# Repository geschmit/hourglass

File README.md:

# Hourglass
Hourglass is a custom PCB watch designed in KiCAD 7.0, to be funded by the Hack Club [OnBoard](https://github.com/hackclub/OnBoard/) grant, which allocates $100 for high schoolers to design and build their own custom PCBs.

## Features
- Accelerometer & Magnetometer for detecting orientation and movement
- 60 individual LEDs for displaying minutes & seconds
- RTC for high-precision timekeeping
- Programmable user buttons
- Revision A:
  - FIDO2 Authentication token
  - USB-C interface
- Revision B:
  - Cheap manufacturing cost

## Revisions
### [Revision A:](./hourglass_reva/) Working design iteration
> `Status: ✔️ (COMPLETE)`

Revision A is the original design, based on the Atmel ATMega32u4 microcontroller. It features a RTC and 9DoF magnetometer-accelerometer to detect orientation, magnetic field strength and more to act as both a device for keeping time and sense when the wearer has raised the watchface to observe. In addition, a USB-C port can allow for interfacing directly to the Mega for uploading code and other functions.

### [Revision B:](./hourglass_revb/) Cost-effective design
> `Status: ✔️ (COMPLETE)`

Revision B is a easier, more affordable option. I'm working on this primarily because revision A is simply too expensive with all peripherals added in to have assembled via JLC's PCBA. It swaps the ATMega32 with an RP2040, the 9DoF magnetometer with split magnetometer & accelerometer ICs, and forgoes the rear battery slot alltogether. The caveat with this is you'll need to wire a battery to the device yourself, but comes at a tremendous discount with the requirement for dual-sided PCB assembly forgone.

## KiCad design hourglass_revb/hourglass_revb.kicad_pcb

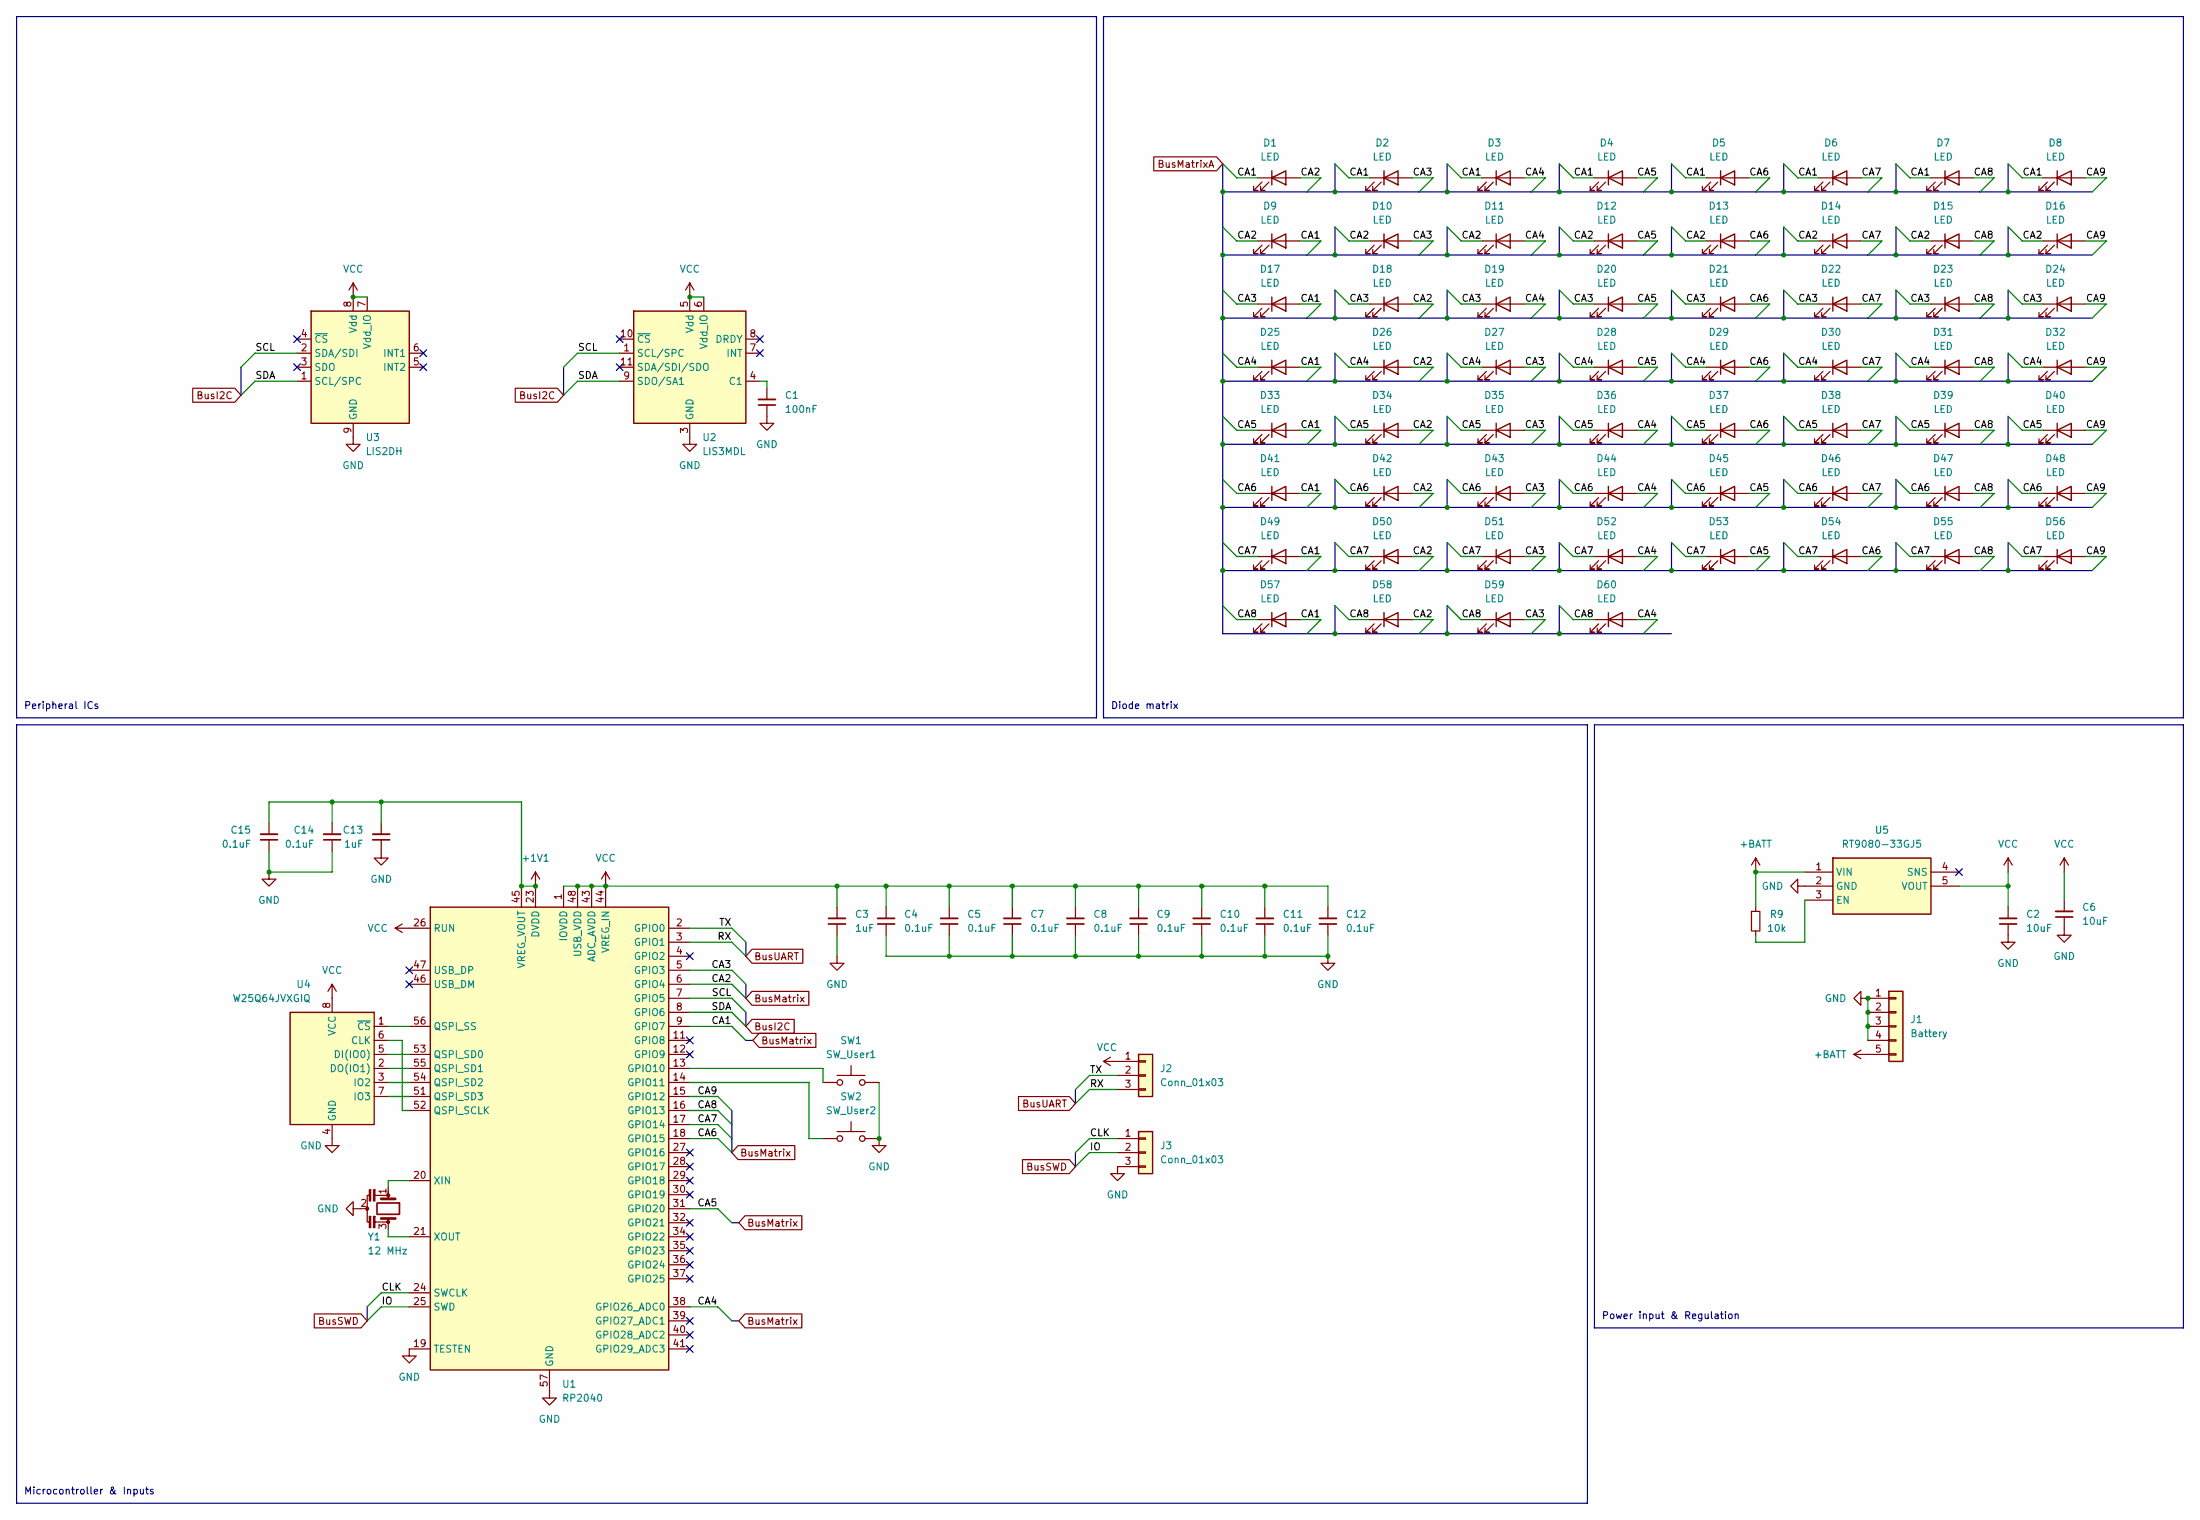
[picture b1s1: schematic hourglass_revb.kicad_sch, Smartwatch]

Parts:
C1: 100nF; C_0201_0603Metric
C2, C6: 10uF; C_0201_0603Metric
C3, C13: 1uF; C_0201_0603Metric
C4, C5, C7, C8, C9, C10, C11, C12, C14, C15: 0.1uF; C_0201_0603Metric
D1, D6, D11, D16, D21, D26, D31, D36, D41, D46, D51, D56: LED; LED_0603_1608Metric
D2, D3, D4, D5, D7, D8, D9, D10, D12, D13, D14, D15, D17, D18, D19, D20, D22, D23, D24, D25, D27, D28, D29, D30, D32, D33, D34, D35, D37, D38, D39, D40, D42, D43, D44, D45, D47, D48, D49, D50, D52, D53, D54, D55, D57, D58, D59, D60: LED; LED_0402_1005Metric
J1: Battery; BAT_BAT-HLD-001-THM
J2, J3: Conn_01x03; PinHeader_1x03_P2.54mm_Vertical
R9: 10k; R_0201_0603Metric
SW1: SW_User1; SW_Push_SPST_NO_Alps_SKRK
SW2: SW_User2; SW_Push_SPST_NO_Alps_SKRK
U1: RP2040; QFN-56-1EP_7x7mm_P0.4mm_EP3.2x3.2mm
U2: LIS3MDL; LGA-12_2x2mm_P0.5mm
U3: LIS2DH; LGA-14_2x2mm_P0.35mm_LayoutBorder3x4y
U4: W25Q64JVXGIQ; WSON-8-1EP_6x5mm_P1.27mm_EP3.4x4.3mm
U5: RT9080-33GJ5; SOT94P280X100-5N; Manufacturer_Part_Number RT9080-33GJ5; Mouser Part Number 835-RT9080-33GJ5
Y1: 12 MHz; ABM8272T3

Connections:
+1V1: C13.2, C14.2, C15.2, U1.23 (DVDD), U1.45 (VREG_VOUT), U1.50 (DVDD)
+BATT: J1.5, R9.1, U5.1 (VIN)
/CA1: D1.1 (K), D2.1 (K), D3.1 (K), D4.1 (K), D5.1 (K), D6.1 (K), D7.1 (K), D8.1 (K), D9.2 (A), D17.2 (A), D25.2 (A), D33.2 (A), D41.2 (A), D49.2 (A), D57.2 (A), U1.9 (GPIO7)
/CA2: D1.2 (A), D9.1 (K), D10.1 (K), D11.1 (K), D12.1 (K), D13.1 (K), D14.1 (K), D15.1 (K), D16.1 (K), D18.2 (A), D26.2 (A), D34.2 (A), D42.2 (A), D50.2 (A), D58.2 (A), U1.6 (GPIO4)
/CA3: D2.2 (A), D10.2 (A), D17.1 (K), D18.1 (K), D19.1 (K), D20.1 (K), D21.1 (K), D22.1 (K), D23.1 (K), D24.1 (K), D27.2 (A), D35.2 (A), D43.2 (A), D51.2 (A), D59.2 (A), U1.5 (GPIO3)
/CA4: D3.2 (A), D11.2 (A), D19.2 (A), D25.1 (K), D26.1 (K), D27.1 (K), D28.1 (K), D29.1 (K), D30.1 (K), D31.1 (K), D32.1 (K), D36.2 (A), D44.2 (A), D52.2 (A), D60.2 (A), U1.38 (GPIO26_ADC0)
/CA5: D4.2 (A), D12.2 (A), D20.2 (A), D28.2 (A), D33.1 (K), D34.1 (K), D35.1 (K), D36.1 (K), D37.1 (K), D38.1 (K), D39.1 (K), D40.1 (K), D45.2 (A), D53.2 (A), U1.31 (GPIO20)
/CA6: D5.2 (A), D13.2 (A), D21.2 (A), D29.2 (A), D37.2 (A), D41.1 (K), D42.1 (K), D43.1 (K), D44.1 (K), D45.1 (K), D46.1 (K), D47.1 (K), D48.1 (K), D54.2 (A), U1.18 (GPIO15)
/CA7: D6.2 (A), D14.2 (A), D22.2 (A), D30.2 (A), D38.2 (A), D46.2 (A), D49.1 (K), D50.1 (K), D51.1 (K), D52.1 (K), D53.1 (K), D54.1 (K), D55.1 (K), D56.1 (K), U1.17 (GPIO14)
/CA8: D7.2 (A), D15.2 (A), D23.2 (A), D31.2 (A), D39.2 (A), D47.2 (A), D55.2 (A), D57.1 (K), D58.1 (K), D59.1 (K), D60.1 (K), U1.16 (GPIO13)
/CA9: D8.2 (A), D16.2 (A), D24.2 (A), D32.2 (A), D40.2 (A), D48.2 (A), D56.2 (A), U1.15 (GPIO12)
/CLK: J3.1, U1.24 (SWCLK)
/IO: J3.2, U1.25 (SWD)
/RX: J2.3, U1.3 (GPIO1)
/SCL: U1.7 (GPIO5), U2.1 (SCL/SPC), U3.2 (SDA/SDI)
/SDA: U1.8 (GPIO6), U2.9 (SDO/SA1), U3.1 (SCL/SPC)
/TX: J2.2, U1.2 (GPIO0)
GND: C1.1, C2.1, C3.1, C4.1, C5.1, C6.1, C7.1, C8.1, C9.1, C10.1, C11.1, C12.1, C13.1, C14.1, C15.1, J1.1, J1.2, J1.3, J1.4, J3.3, SW1.2, SW2.2, U1.19 (TESTEN), U1.57 (GND), U2.2 (GND), U2.3 (GND), U2.12 (GND), U3.9 (GND), U3.10 (GND), U3.11 (GND), U3.12 (GND), U3.13 (GND), U3.14 (GND), U4.4 (GND), U5.2 (GND), Y1.2
unnamed: SW1.1, U1.13 (GPIO10)
unnamed: SW2.1, U1.14 (GPIO11)
unnamed: U1.52 (QSPI_SCLK), U4.6 (CLK)
unnamed: U1.53 (QSPI_SD0), U4.5 (DI(IO0))
unnamed: U1.55 (QSPI_SD1), U4.2 (DO(IO1))
unnamed: U1.54 (QSPI_SD2), U4.3 (IO2)
unnamed: U1.51 (QSPI_SD3), U4.7 (IO3)
unnamed: U1.56 (QSPI_SS), U4.1 (~CS)
unnamed: U1.20 (XIN), Y1.1
unnamed: U1.21 (XOUT), Y1.3
unnamed: C1.2, U2.4 (C1)
unnamed: R9.2, U5.3 (EN)
VCC: C2.2, C3.2, C4.2, C5.2, C6.2, C7.2, C8.2, C9.2, C10.2, C11.2, C12.2, J2.1, U1.1 (IOVDD), U1.10 (IOVDD), U1.22 (IOVDD), U1.26 (RUN), U1.33 (IOVDD), U1.42 (IOVDD), U1.43 (ADC_AVDD), U1.44 (VREG_IN), U1.48 (USB_VDD), U1.49 (IOVDD), U2.5 (Vdd), U2.6 (Vdd_IO), U3.7 (Vdd_IO), U3.8 (Vdd), U4.8 (VCC), U5.5 (VOUT)

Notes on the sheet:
Power input & Regulation
Diode matrix
Peripheral ICs
Microcontroller & Inputs

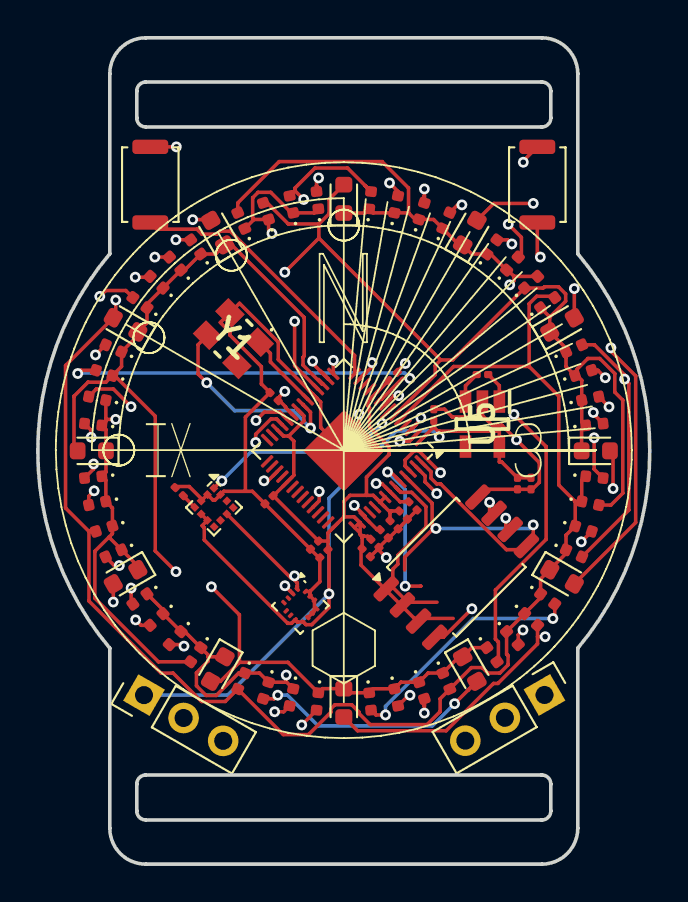
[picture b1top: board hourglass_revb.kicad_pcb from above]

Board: 4 copper layers, 34.0 x 45.9 mm, 87 parts (1 on the bottom side), 31 nets.

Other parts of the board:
kibuzzard-66C6528B: G***; kibuzzard-66C6528B

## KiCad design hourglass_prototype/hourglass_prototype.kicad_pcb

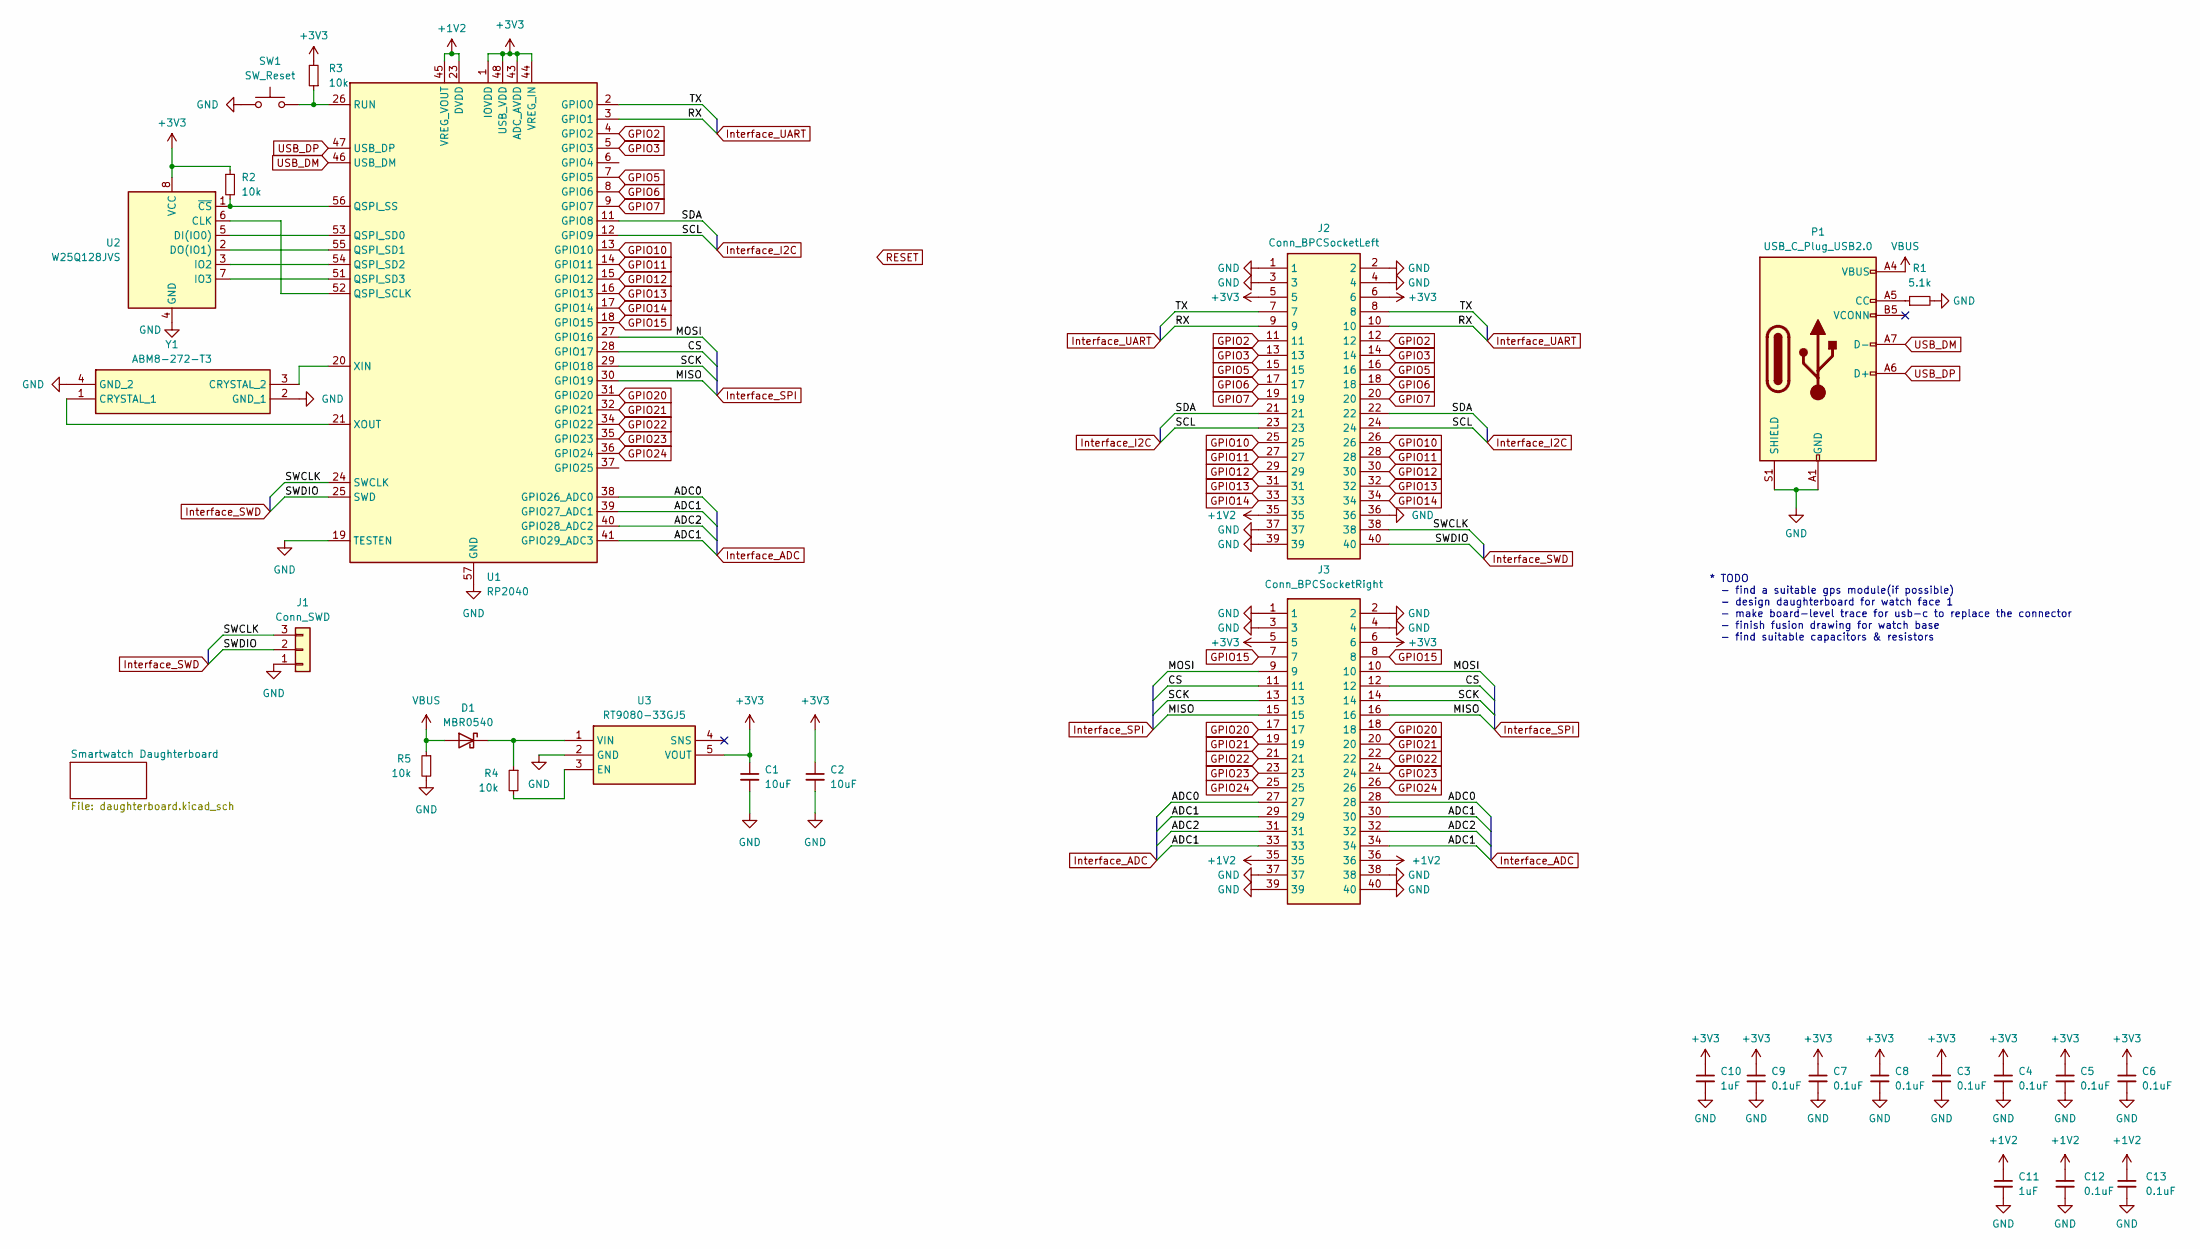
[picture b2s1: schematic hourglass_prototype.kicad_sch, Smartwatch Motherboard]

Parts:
C1, C2: 10uF; C_0201_0603Metric
C3, C4, C5, C6, C7, C8, C9, C12, C13: 0.1uF; C_0201_0603Metric
C10, C11: 1uF; C_0201_0603Metric
D1: MBR0540; D_SOD-123
J1: Conn_SWD; JST_SH_BM03B-SRSS-TB_1x03-1MP_P1.00mm_Vertical
J2: Conn_BPCSocketLeft; DF40HC3040DS04V51; Manufacturer_Part_Number DF40HC(3.0)-40DS-0.4V(51); Mouser Part Number 798-DF40HC3040DS04V5
J3: Conn_BPCSocketRight; DF40HC3040DS04V51; Manufacturer_Part_Number DF40HC(3.0)-40DS-0.4V(51); Mouser Part Number 798-DF40HC3040DS04V5
P1: USB_C_Plug_USB2.0; USB_C_Receptacle_GCT_USB4105-xx-A_16P_TopMnt_Horizontal
R1: 5.1k; R_0201_0603Metric
R2, R3, R4, R5: 10k; R_0201_0603Metric
SW1: SW_Reset
U1: RP2040; QFN-56-1EP_7x7mm_P0.4mm_EP3.2x3.2mm
U2: W25Q128JVS; SOIC127P790X216-8N
U3: RT9080-33GJ5; SOT94P280X100-5N; Manufacturer_Part_Number RT9080-33GJ5; Mouser Part Number 835-RT9080-33GJ5
Y1: ABM8-272-T3; ABM8272T3; Manufacturer_Part_Number ABM8-272-T3; Mouser Part Number 815-ABM8-272-T3

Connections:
+3V3: C1.1, C2.1, C3.1, C4.1, C5.1, C6.1, C7.1, C8.1, C9.1, C10.1, J2.5, J2.6, J3.5, J3.6, R2.1, R3.2, U1.1 (IOVDD), U1.10 (IOVDD), U1.22 (IOVDD), U1.33 (IOVDD), U1.42 (IOVDD), U1.43 (ADC_AVDD), U1.44 (VREG_IN), U1.48 (USB_VDD), U1.49 (IOVDD), U2.8 (VCC), U3.5 (VOUT); also elsewhere on the board
/ADC0: J3.27, J3.28, U1.38 (GPIO26_ADC0)
/ADC2: J3.31, J3.32, U1.40 (GPIO28_ADC2)
/CS: J3.11, J3.12, U1.28 (GPIO17)
/MISO: J3.15, J3.16, U1.30 (GPIO19)
/MOSI: J3.9, J3.10, U1.27 (GPIO16)
/RX: J2.9, J2.10, U1.3 (GPIO1)
/SCK: J3.13, J3.14, U1.29 (GPIO18)
/SCL: J2.23, J2.24, U1.12 (GPIO9)
/SDA: J2.21, J2.22, U1.11 (GPIO8)
/SWCLK: J1.3, J2.38, U1.24 (SWCLK)
/SWDIO: J1.2, J2.40, U1.25 (SWD)
/TX: J2.7, J2.8, U1.2 (GPIO0)
GPIO2: J2.11, J2.12, U1.4 (GPIO2); also elsewhere on the board
GPIO3: J2.13, J2.14, U1.5 (GPIO3); also elsewhere on the board
GPIO5: J2.15, J2.16, U1.7 (GPIO5); also elsewhere on the board
GPIO6: J2.17, J2.18, U1.8 (GPIO6); also elsewhere on the board
GPIO7: J2.19, J2.20, U1.9 (GPIO7); also elsewhere on the board
GPIO10: J2.25, J2.26, U1.13 (GPIO10); also elsewhere on the board
GPIO11: J2.27, J2.28, U1.14 (GPIO11); also elsewhere on the board
GPIO12: J2.29, J2.30, U1.15 (GPIO12); also elsewhere on the board
GPIO13: J2.31, J2.32, U1.16 (GPIO13); also elsewhere on the board
GPIO14: J2.33, J2.34, U1.17 (GPIO14); also elsewhere on the board
GPIO15: J3.7, J3.8, U1.18 (GPIO15); also elsewhere on the board
GPIO20: J3.17, J3.18, U1.31 (GPIO20); also elsewhere on the board
GPIO21: J3.19, J3.20, U1.32 (GPIO21); also elsewhere on the board
GPIO22: J3.21, J3.22, U1.34 (GPIO22); also elsewhere on the board
GPIO23: J3.23, J3.24, U1.35 (GPIO23); also elsewhere on the board
GPIO24: J3.25, J3.26, U1.36 (GPIO24); also elsewhere on the board
unnamed: D1.1 (K), R4.1, U3.1 (VIN)
unnamed: P1.A5 (CC), R1.1
unnamed: U1.52 (QSPI_SCLK), U2.6 (CLK)
unnamed: U1.53 (QSPI_SD0), U2.5 (DI(IO0))
unnamed: U1.55 (QSPI_SD1), U2.2 (DO(IO1))
unnamed: U1.54 (QSPI_SD2), U2.3 (IO2)
unnamed: U1.51 (QSPI_SD3), U2.7 (IO3)
unnamed: R2.2, U1.56 (QSPI_SS), U2.1 (~CS)
unnamed: R3.1, SW1.2, U1.26 (RUN)
unnamed: U1.20 (XIN), Y1.3 (CRYSTAL_2)
unnamed: U1.21 (XOUT), Y1.1 (CRYSTAL_1)
unnamed: R4.2, U3.3 (EN)
USB_DM: P1.A7 (D-), U1.46 (USB_DM)
USB_DP: P1.A6 (D+), U1.47 (USB_DP)
VBUS: D1.2 (A), P1.A4 (VBUS), P1.A9 (VBUS), P1.B4 (VBUS), P1.B9 (VBUS), R5.1

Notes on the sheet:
* TODO - find a suitable gps module(if possible) - design daughterboard for watch face 1 - make board-level trace for usb-c to replace the connector - finish fusion drawing for watch base - find suitable capacitors & resistors

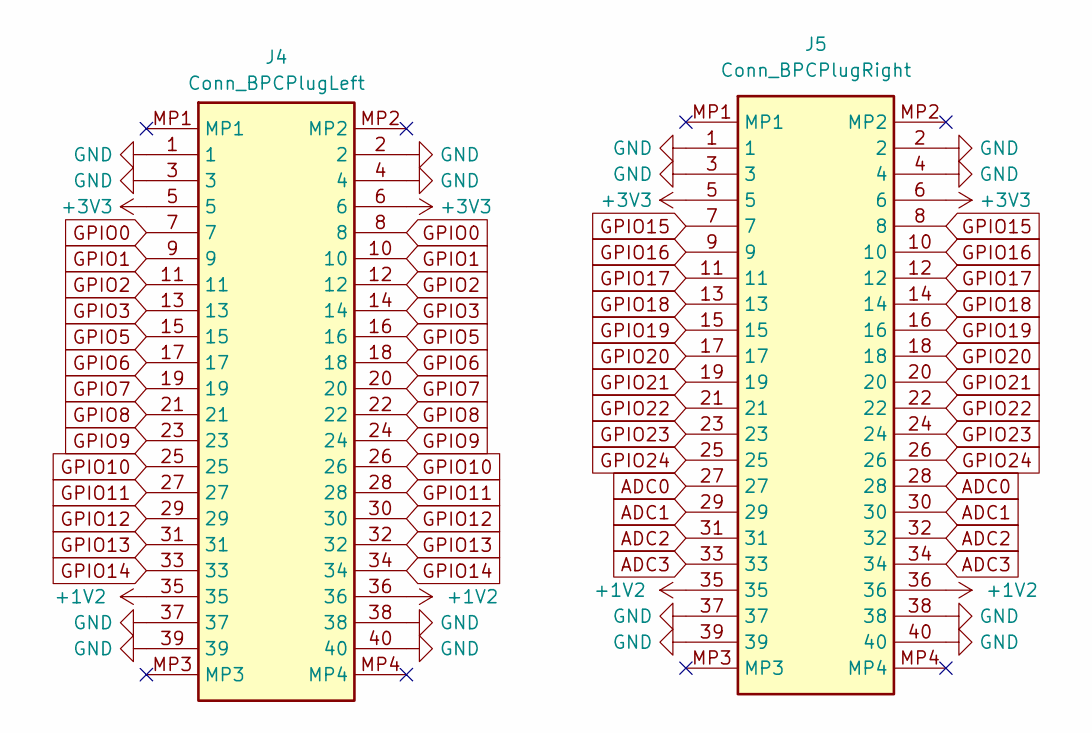
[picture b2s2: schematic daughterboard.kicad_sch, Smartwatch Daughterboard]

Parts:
J4: Conn_BPCPlugLeft; DF40C40DP04V51; Manufacturer_Part_Number DF40C-40DP-0.4V(51); Mouser Part Number 798-DF40C40DP0.4V51
J5: Conn_BPCPlugRight; DF40C40DP04V51; Manufacturer_Part_Number DF40C-40DP-0.4V(51); Mouser Part Number 798-DF40C40DP0.4V51

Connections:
+3V3: J4.5, J4.6, J5.5, J5.6; also elsewhere on the board
ADC0: J5.27, J5.28
ADC1: J5.29, J5.30
ADC2: J5.31, J5.32
ADC3: J5.33, J5.34
GPIO0: J4.7, J4.8
GPIO1: J4.9, J4.10
GPIO2: J4.11, J4.12; also elsewhere on the board
GPIO3: J4.13, J4.14; also elsewhere on the board
GPIO5: J4.15, J4.16; also elsewhere on the board
GPIO6: J4.17, J4.18; also elsewhere on the board
GPIO7: J4.19, J4.20; also elsewhere on the board
GPIO8: J4.21, J4.22
GPIO9: J4.23, J4.24
GPIO10: J4.25, J4.26; also elsewhere on the board
GPIO11: J4.27, J4.28; also elsewhere on the board
GPIO12: J4.29, J4.30; also elsewhere on the board
GPIO13: J4.31, J4.32; also elsewhere on the board
GPIO14: J4.33, J4.34; also elsewhere on the board
GPIO15: J5.7, J5.8; also elsewhere on the board
GPIO16: J5.9, J5.10
GPIO17: J5.11, J5.12
GPIO18: J5.13, J5.14
GPIO19: J5.15, J5.16
GPIO20: J5.17, J5.18; also elsewhere on the board
GPIO21: J5.19, J5.20; also elsewhere on the board
GPIO22: J5.21, J5.22; also elsewhere on the board
GPIO23: J5.23, J5.24; also elsewhere on the board
GPIO24: J5.25, J5.26; also elsewhere on the board

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
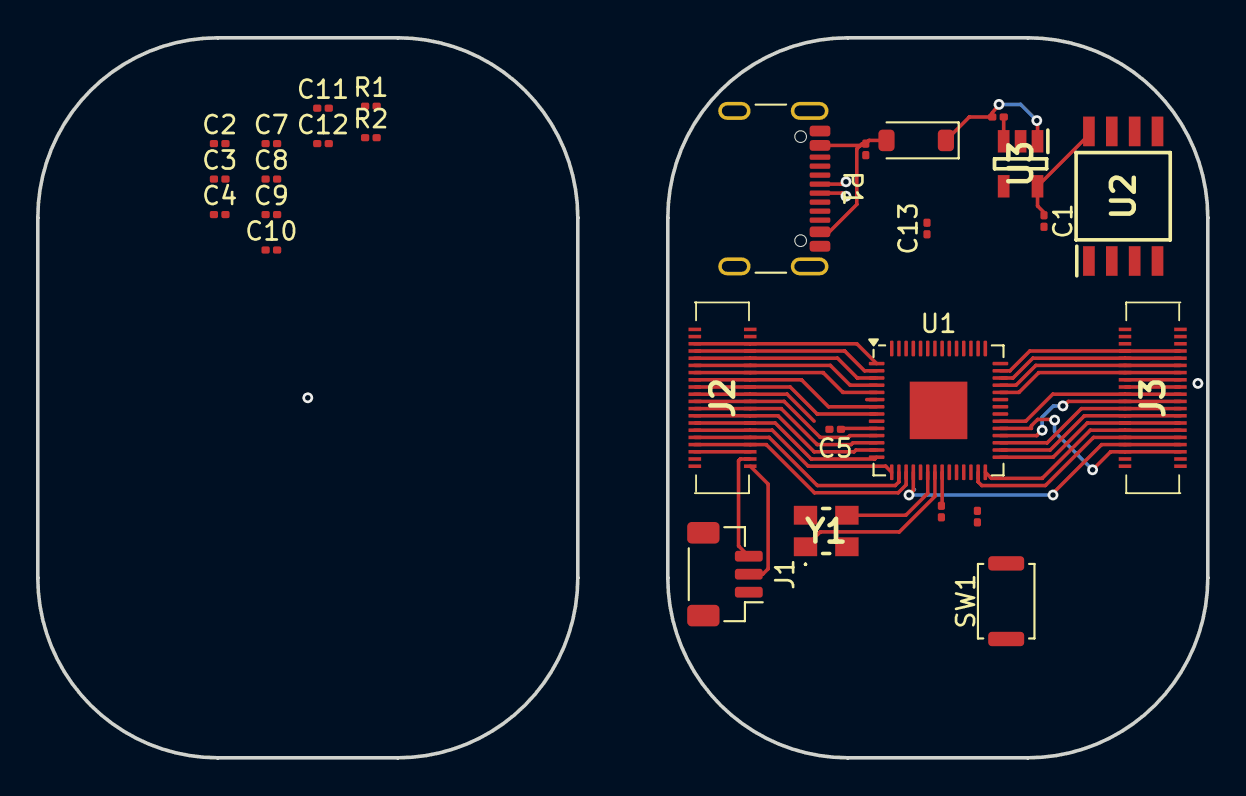
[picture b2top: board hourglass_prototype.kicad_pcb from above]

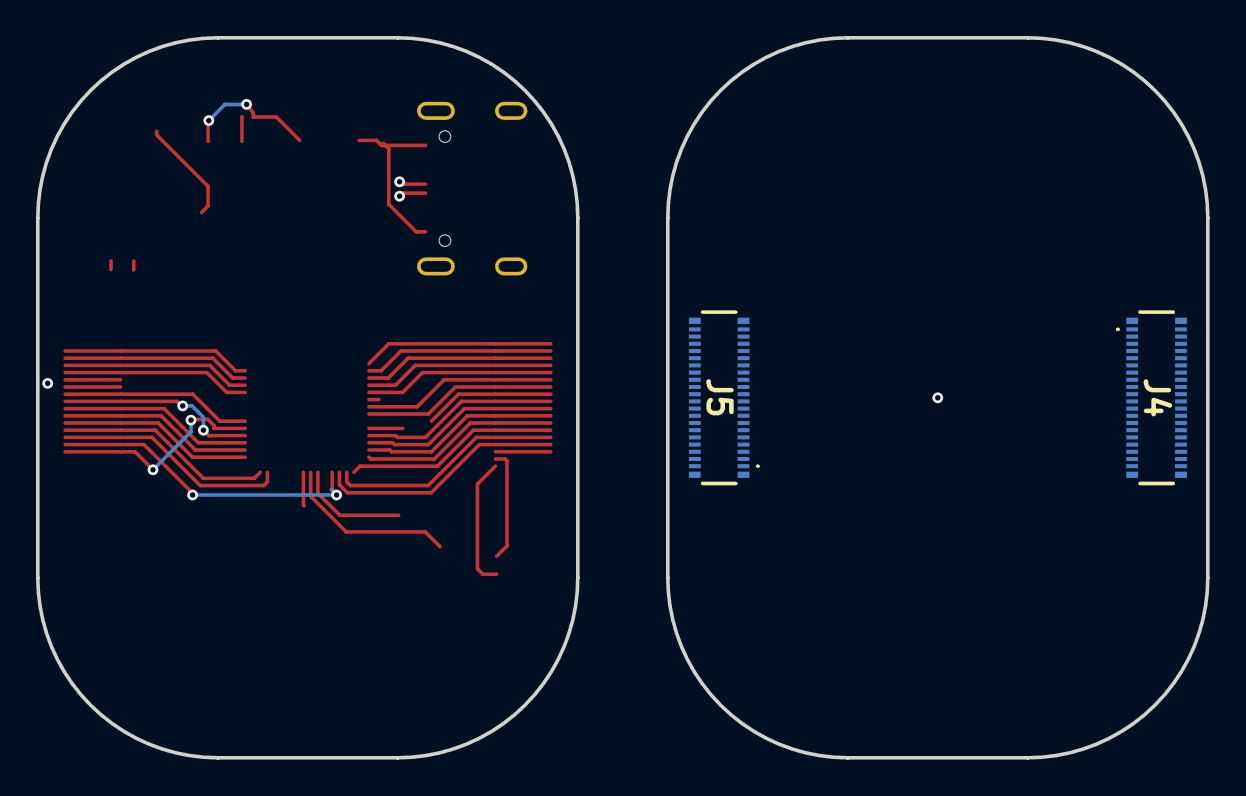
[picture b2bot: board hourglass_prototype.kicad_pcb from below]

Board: 2 copper layers, 65.0 x 40.0 mm, 30 parts (2 on the bottom side), 60 nets.

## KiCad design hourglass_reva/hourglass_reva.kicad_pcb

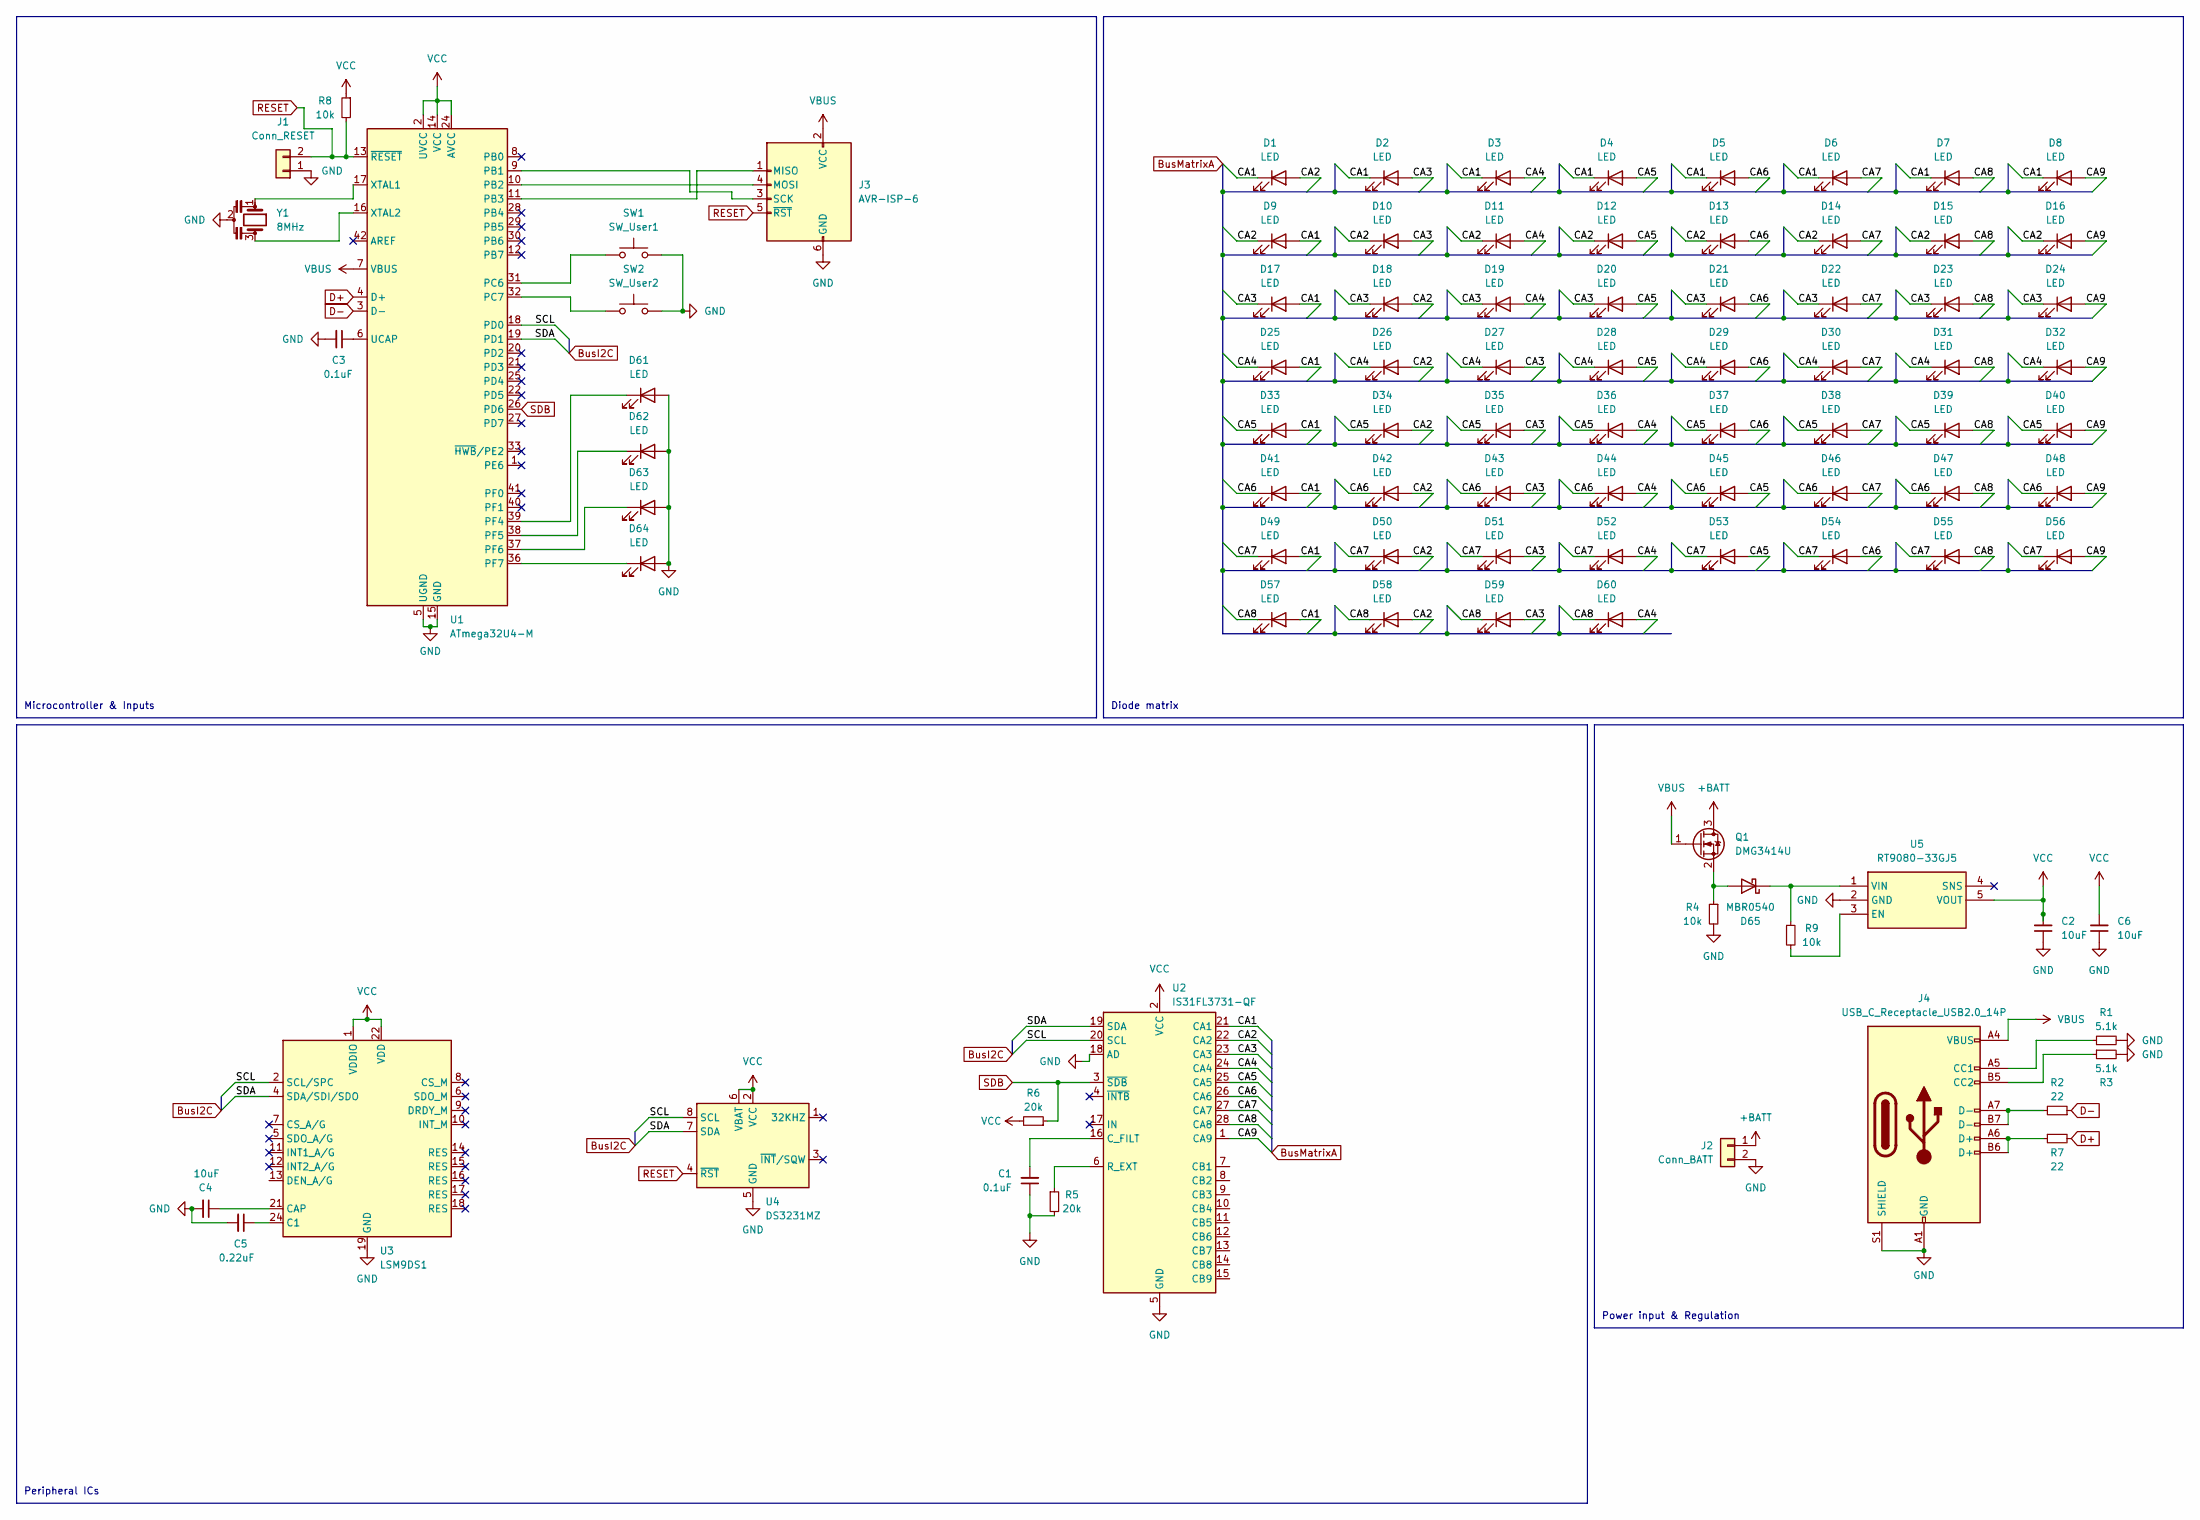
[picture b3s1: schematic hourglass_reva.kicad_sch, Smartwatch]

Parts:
C1, C3: 0.1uF; C_0201_0603Metric
C2, C4, C6: 10uF; C_0201_0603Metric
C5: 0.22uF; C_0201_0603Metric
D1, D6, D11, D16, D21, D26, D31, D36, D41, D46, D51, D56: LED; LED_0603_1608Metric
D2, D3, D4, D5, D7, D8, D9, D10, D12, D13, D14, D15, D17, D18, D19, D20, D22, D23, D24, D25, D27, D28, D29, D30, D32, D33, D34, D35, D37, D38, D39, D40, D42, D43, D44, D45, D47, D48, D49, D50, D52, D53, D54, D55, D57, D58, D59, D60, D61, D62, D63, D64: LED; LED_0402_1005Metric
D65: MBR0540; D_SOD-123
J1: Conn_RESET; PinHeader_1x02_P1.00mm_Vertical
J2: Conn_BATT; BatteryHolder_LINX_BAT-HLD-012-SMT
J3: AVR-ISP-6; PinHeader_2x03_P1.27mm_Vertical
J4: USB_C_Receptacle_USB2.0_14P; USB_C_Receptacle_GCT_USB4110
Q1: DMG3414U; SOT-23
R1, R3: 5.1k; R_0201_0603Metric
R2, R7: 22; R_0201_0603Metric
R4, R8, R9: 10k; R_0201_0603Metric
R5, R6: 20k; R_0201_0603Metric
SW1: SW_User1; SW_Push_SPST_NO_Alps_SKRK
SW2: SW_User2; SW_Push_SPST_NO_Alps_SKRK
U1: ATmega32U4-M; QFN-44-1EP_7x7mm_P0.5mm_EP5.2x5.2mm
U2: IS31FL3731-QF; QFN-28-1EP_4x4mm_P0.4mm_EP2.3x2.3mm
U3: LSM9DS1; LGA-24L_3x3.5mm_P0.43mm
U4: DS3231MZ; SOIC-8_3.9x4.9mm_P1.27mm
U5: RT9080-33GJ5; SOT94P280X100-5N; Manufacturer_Part_Number RT9080-33GJ5; Mouser Part Number 835-RT9080-33GJ5
Y1: 8MHz; Crystal_SMD_3225-4Pin_3.2x2.5mm

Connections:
+BATT: J2.1, Q1.3 (D)
/CA1: D1.1 (K), D2.1 (K), D3.1 (K), D4.1 (K), D5.1 (K), D6.1 (K), D7.1 (K), D8.1 (K), D9.2 (A), D17.2 (A), D25.2 (A), D33.2 (A), D41.2 (A), D49.2 (A), D57.2 (A), U2.21 (CA1)
/CA2: D1.2 (A), D9.1 (K), D10.1 (K), D11.1 (K), D12.1 (K), D13.1 (K), D14.1 (K), D15.1 (K), D16.1 (K), D18.2 (A), D26.2 (A), D34.2 (A), D42.2 (A), D50.2 (A), D58.2 (A), U2.22 (CA2)
/CA3: D2.2 (A), D10.2 (A), D17.1 (K), D18.1 (K), D19.1 (K), D20.1 (K), D21.1 (K), D22.1 (K), D23.1 (K), D24.1 (K), D27.2 (A), D35.2 (A), D43.2 (A), D51.2 (A), D59.2 (A), U2.23 (CA3)
/CA4: D3.2 (A), D11.2 (A), D19.2 (A), D25.1 (K), D26.1 (K), D27.1 (K), D28.1 (K), D29.1 (K), D30.1 (K), D31.1 (K), D32.1 (K), D36.2 (A), D44.2 (A), D52.2 (A), D60.2 (A), U2.24 (CA4)
/CA5: D4.2 (A), D12.2 (A), D20.2 (A), D28.2 (A), D33.1 (K), D34.1 (K), D35.1 (K), D36.1 (K), D37.1 (K), D38.1 (K), D39.1 (K), D40.1 (K), D45.2 (A), D53.2 (A), U2.25 (CA5)
/CA6: D5.2 (A), D13.2 (A), D21.2 (A), D29.2 (A), D37.2 (A), D41.1 (K), D42.1 (K), D43.1 (K), D44.1 (K), D45.1 (K), D46.1 (K), D47.1 (K), D48.1 (K), D54.2 (A), U2.26 (CA6)
/CA7: D6.2 (A), D14.2 (A), D22.2 (A), D30.2 (A), D38.2 (A), D46.2 (A), D49.1 (K), D50.1 (K), D51.1 (K), D52.1 (K), D53.1 (K), D54.1 (K), D55.1 (K), D56.1 (K), U2.27 (CA7)
/CA8: D7.2 (A), D15.2 (A), D23.2 (A), D31.2 (A), D39.2 (A), D47.2 (A), D55.2 (A), D57.1 (K), D58.1 (K), D59.1 (K), D60.1 (K), U2.28 (CA8)
/CA9: D8.2 (A), D16.2 (A), D24.2 (A), D32.2 (A), D40.2 (A), D48.2 (A), D56.2 (A), U2.1 (CA9)
/SCL: U1.18 (PD0), U2.20 (SCL), U3.2 (SCL/SPC), U4.8 (SCL)
/SDA: U1.19 (PD1), U2.19 (SDA), U3.4 (SDA/SDI/SDO), U4.7 (SDA)
D+: R7.2, U1.4 (D+)
D-: R2.1, U1.3 (D-)
GND: C1.1, C2.1, C3.2, C4.2, C5.2, C6.1, D61.2 (A), D62.2 (A), D63.2 (A), D64.2 (A), J1.1, J2.2, J3.6 (GND), J4.A1 (GND), J4.A12 (GND), J4.B1 (GND), J4.B12 (GND), J4.S1 (SHIELD), R1.2, R3.2, R4.2, R5.2, SW1.2, SW2.2, U1.5 (UGND), U1.15 (GND), U1.23 (GND), U1.35 (GND), U1.43 (GND), U1.45 (GND), U2.5 (GND), U2.18 (AD), U2.29 (GND), U3.19 (GND), U3.20 (GND), U4.5 (GND), U5.2 (GND), Y1.2
unnamed: D61.1 (K), U1.39 (PF4)
unnamed: D62.1 (K), U1.38 (PF5)
unnamed: D63.1 (K), U1.37 (PF6)
unnamed: D64.1 (K), U1.36 (PF7)
unnamed: D65.2 (A), Q1.2 (S), R4.1
unnamed: D65.1 (K), R9.1, U5.1 (VIN)
unnamed: J3.1 (MISO), U1.11 (PB3)
unnamed: J3.4 (MOSI), U1.10 (PB2)
unnamed: J3.3 (SCK), U1.9 (PB1)
unnamed: J4.A5 (CC1), R1.1
unnamed: J4.B5 (CC2), R3.1
unnamed: J4.A6 (D+), J4.B6 (D+), R7.1
unnamed: J4.A7 (D-), J4.B7 (D-), R2.2
unnamed: SW1.1, U1.31 (PC6)
unnamed: SW2.1, U1.32 (PC7)
unnamed: C3.1, U1.6 (UCAP)
unnamed: U1.17 (XTAL1), Y1.1
unnamed: U1.16 (XTAL2), Y1.3
unnamed: C1.2, U2.16 (C_FILT)
unnamed: R5.1, U2.6 (R_EXT)
unnamed: C5.1, U3.24 (C1)
unnamed: C4.1, U3.21 (CAP)
unnamed: R9.2, U5.3 (EN)
RESET: J1.2, J3.5 (~RST), R8.2, U1.13 (~RESET), U4.4 (~RST)
SDB: R6.1, U1.26 (PD6), U2.3 (~SDB)
VBUS: J3.2 (VCC), J4.A4 (VBUS), J4.A9 (VBUS), J4.B4 (VBUS), J4.B9 (VBUS), Q1.1 (G), U1.7 (VBUS)
VCC: C2.2, C6.2, R6.2, R8.1, U1.2 (UVCC), U1.14 (VCC), U1.24 (AVCC), U1.34 (VCC), U1.44 (AVCC), U2.2 (VCC), U3.1 (VDDIO), U3.3 (VDDIO), U3.22 (VDD), U3.23 (VDD), U4.2 (VCC), U4.6 (VBAT), U5.5 (VOUT)

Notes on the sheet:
Power input & Regulation
Diode matrix
Peripheral ICs
Microcontroller & Inputs
